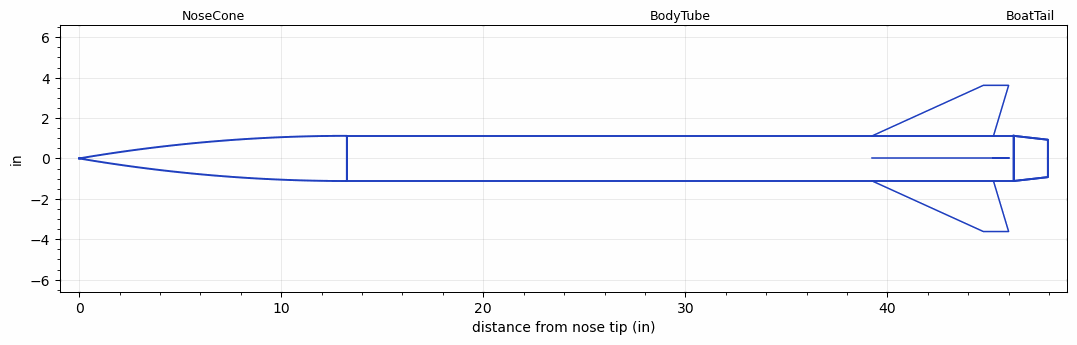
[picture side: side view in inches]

<RASAeroDocument>
 <FileVersion>2</FileVersion>
 <RocketDesign>
  <NoseCone>
   <Length>13.25</Length>
   <Diameter>2.23622</Diameter>
   <Shape>Tangent Ogive</Shape>
   <Location>0</Location>
  </NoseCone>
  <BodyTube>
   <Length>33</Length>
   <Diameter>2.23622</Diameter>
   <Location>13.25</Location>
   <BoattailLength>1.693</BoattailLength>
   <BoattailRearDiameter>1.85</BoattailRearDiameter>
   <Fin>
    <Count>4</Count>
    <Chord>6</Chord>
    <Span>2.5</Span>
    <SweepDistance>5.5</SweepDistance>
    <TipChord>1.25</TipChord>
    <Thickness>0.125</Thickness>
    <Location>7</Location>
    <AirfoilSection>Square</AirfoilSection>
   </Fin>
  </BodyTube>
  <BoatTail>
   <Length>1.693</Length>
   <Diameter>2.23622</Diameter>
   <RearDiameter>1.85</RearDiameter>
   <Location>46.25</Location>
  </BoatTail>
  <Surface>Polished</Surface>
  <ModifiedBarrowman>True</ModifiedBarrowman>
  <Turbulence>False</Turbulence>
  <UseBooster1>False</UseBooster1>
  <UseBooster2>False</UseBooster2>
 </RocketDesign>
 <LaunchSite>
  <Altitude>2500</Altitude>
  <Pressure>0</Pressure>
  <RodAngle>0</RodAngle>
  <RodLength>7</RodLength>
  <Temperature>80</Temperature>
  <WindSpeed>0</WindSpeed>
 </LaunchSite>
 <Recovery>
  <Altitude1>1000</Altitude1>
  <Altitude2>1000</Altitude2>
  <DeviceType1>Parachute</DeviceType1>
  <DeviceType2>Parachute</DeviceType2>
  <Event1>True</Event1>
  <Event2>True</Event2>
  <Size1>18</Size1>
  <Size2>36</Size2>
  <EventType1>Apogee</EventType1>
  <EventType2>Altitude</EventType2>
  <CD1>1.33</CD1>
  <CD2>1.33</CD2>
 </Recovery>
 <SimulationList>
  <Simulation>
   <SustainerEngine>K805G  (AT)</SustainerEngine>
   <SustainerLaunchWt>7.3</SustainerLaunchWt>
   <SustainerCG>31</SustainerCG>
   <SustainerIgnitionDelay>0</SustainerIgnitionDelay>
   <Booster1SeparationDelay>0</Booster1SeparationDelay>
   <Booster1IgnitionDelay>0</Booster1IgnitionDelay>
   <IncludeBooster1>False</IncludeBooster1>
   <Booster2Delay>0</Booster2Delay>
   <IncludeBooster2>False</IncludeBooster2>
   <TimetoApogee>23.90045</TimetoApogee>
   <MaxAltitude>12403.72</MaxAltitude>
   <MaxVelocity>1636.344</MaxVelocity>
   <OptimumWt>6.570001</OptimumWt>
   <OptimumMaxAlt>6.570001</OptimumMaxAlt>
  </Simulation>
  <Simulation>
   <SustainerEngine>K805G  (AT)</SustainerEngine>
   <SustainerLaunchWt>7.3</SustainerLaunchWt>
   <SustainerNozzleDiameter>0.75</SustainerNozzleDiameter>
   <SustainerCG>31.5</SustainerCG>
   <SustainerIgnitionDelay>0</SustainerIgnitionDelay>
   <Booster1SeparationDelay>0</Booster1SeparationDelay>
   <Booster1IgnitionDelay>0</Booster1IgnitionDelay>
   <IncludeBooster1>False</IncludeBooster1>
   <Booster2Delay>0</Booster2Delay>
   <IncludeBooster2>False</IncludeBooster2>
   <TimetoApogee>23.95045</TimetoApogee>
   <MaxAltitude>12477.66</MaxAltitude>
   <MaxVelocity>1647.213</MaxVelocity>
  </Simulation>
 </SimulationList>
</RASAeroDocument>
